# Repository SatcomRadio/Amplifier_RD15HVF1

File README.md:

# RD15HVF1 Amplifier for 280-320 mhz

This repo consists of a board that uses the RD15HVF1 amplifier at satcom frequency range (280-320Mhz).  

#### Please make sure to visit the [satcom radio website](https://satcomradio.github.io/) for more information

------

## Important notes:

- Do not put more than 6W of input RF power. The max power output of this PA is around 20W. Check the datasheet.
- You will need a tx/rx swith if you want to recieve when using this amplifier and also a lowpass filter to avoid it's harmonics!
- The recomended vias voltage is 2.7v. **Before soldering the amplifier adjust the potentiometer!**

- There are **a lot** of fake RD15HVF1 chips on aliexpress!  
- It's better to buy a used RD15HVF1 with the legs cut (as in [here](https://aliexpress.com/item/1005008441262750.html) than take the risk of buying a "new" one that is fake.

## Features:

- With 4W at 300mhz it gives an output of around 23W at 13.8v
- The input SWR is well tunned

## Aditional information:

- Be sure to use a proper heatsink. Ideally it should be 100x50mm. [This](https://aliexpress.com/item/1005004879389236.html) is the one I've got

- Apply thermal paste between the `RD15HVF1` amplifier and the heatsink
- The wound coils act as RF chokes. They should have between 150-300nH so wound a 0.7mm enameled wire around a 5mm drill bit for 6 turns
- The zener diode acts as a voltage limiter. Buy one with a breakdown voltage of around 4v so even if the potentiometer is open it will not push to the bias the 9v of the voltage regulator
- If the amplifier is not properly bolted to the heatsink or the coils are not correct, the output power will oscilate.
- If you buy one of those cheap black amplifiers of 4W for HF,VHF on aliexpress and connect a hackrf to it before connecting it to this amplifier, you'll get an output power of around 16W.
------

## Ordering the PCB:

Download the [GERBER-Amplifier](./GERBER-Amplifier.zip) file from this repo and order it a jlcpcb with the default options.  
The only option I've changed is to remove the manufacture code mark

------

## Prototype image:

------

## Output power:

### 2W input

| Freq in Mhz | Output power (W) |
|-------------|------------------|
| 270 | 14.3 |
| 280 | 16.5 |
| 290 | 15.5 |
| 300 | 14.5 |
| 310 | 14.1 |
| 320 | 13.3 |

At 4W input power the output is >20W

------

## BOM:

```
- PCB that you can order ar jlcpcb or somewhere else.
- RD15HVF1 (https://aliexpress.com/item/1005008441262750.html)
- 0805 560p Capacitor
- 0805 27p Capacitor
- 0805 62p Capacitor
- 0805 36p Capacitor
- 0805 8p Capacitor
- 0805 100p Capacitor
- 2x 1812 100n Capacitor
- 2x 1812 1u Capacitor
- 0805 10 ohm resistor
- 0805 1k ohm resistor
- L7809  9v voltage regulator
- 33uF SMD electrolitic cap 25v 5X5.4mm (https://aliexpress.com/item/1005005427427871.html)
- 3314G 10k potentiometer (https://aliexpress.com/item/1005003118598266.html)
- 100x50x50mm heatsink (https://aliexpress.com/item/1005004879389236.html)
- 0.7mm enameled wire for making air wound coils
- 2x SMA connectors
- (Optional) LL41 SMD 3v9 or 4v7 Zener Diode (Voltage limiter)
```

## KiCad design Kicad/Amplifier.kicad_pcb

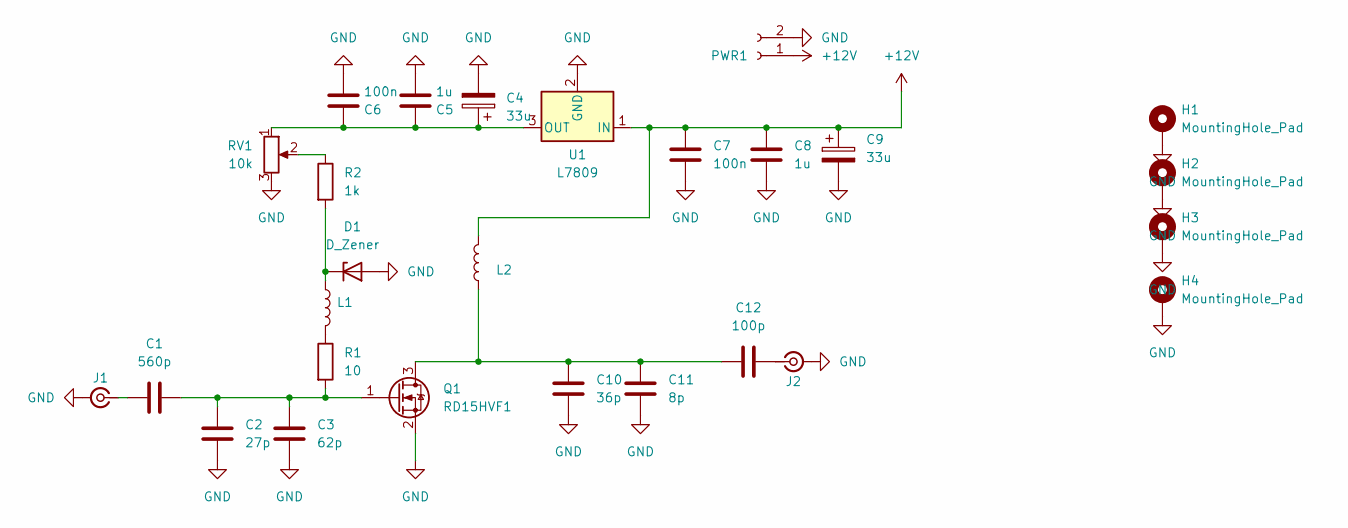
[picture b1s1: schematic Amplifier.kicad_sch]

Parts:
C1: 560p; C_0805_2012Metric_Pad1.18x1.45mm_HandSolder
C2: 27p; C_0805_2012Metric_Pad1.18x1.45mm_HandSolder
C3: 62p; C_0805_2012Metric_Pad1.18x1.45mm_HandSolder
C4, C9: 33u; CP_Elec_5x5.4
C5, C8: 1u; C_1812_4532Metric_Pad1.57x3.40mm_HandSolder
C6, C7: 100n; C_1812_4532Metric_Pad1.57x3.40mm_HandSolder
C10: 36p; C_0805_2012Metric_Pad1.18x1.45mm_HandSolder
C11: 8p; C_0805_2012Metric_Pad1.18x1.45mm_HandSolder
C12: 100p; C_0805_2012Metric_Pad1.18x1.45mm_HandSolder
D1: D_Zener; D_MiniMELF_Handsoldering
H1, H2, H3, H4: MountingHole_Pad; MountingHole_3.2mm_M3_DIN965_Pad
J1, J2: SMA_Samtec_SMA-J-P-X-ST-EM1_EdgeMount
L1, L2: 300n; Wound_Inductor_L
PWR1: Conn_01x02_Socket; Power_Conn
Q1: RD15HVF1; TO-220 SMD
R1: 10; R_0805_2012Metric_Pad1.20x1.40mm_HandSolder
R2: 1k; R_0805_2012Metric_Pad1.20x1.40mm_HandSolder
RV1: 10k; Potentiometer_Bourns_3314G_Vertical
U1: L7809; TO-220 SMD

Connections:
+12V: C7.2, C8.2, C9.1, L2.2, PWR1.1, U1.1 (IN)
GND: C2.1, C3.1, C4.2, C5.1, C6.1, C7.1, C8.1, C9.2, C10.1, C11.1, D1.2 (A), H1.1, H2.1, H3.1, H4.1, J1.2 (Ext), J2.2 (Ext), PWR1.2, Q1.2 (S), RV1.3, U1.2 (GND)
unnamed: D1.1 (K), L1.1, R2.2
unnamed: C1.1, J1.1 (In)
unnamed: C12.2, J2.1 (In)
unnamed: L1.2, R1.1
unnamed: C10.2, C11.2, C12.1, L2.1, Q1.3 (D)
unnamed: C1.2, C2.2, C3.2, Q1.1 (G), R1.2
unnamed: R2.1, RV1.2
unnamed: C4.1, C5.2, C6.2, RV1.1, U1.3 (OUT)

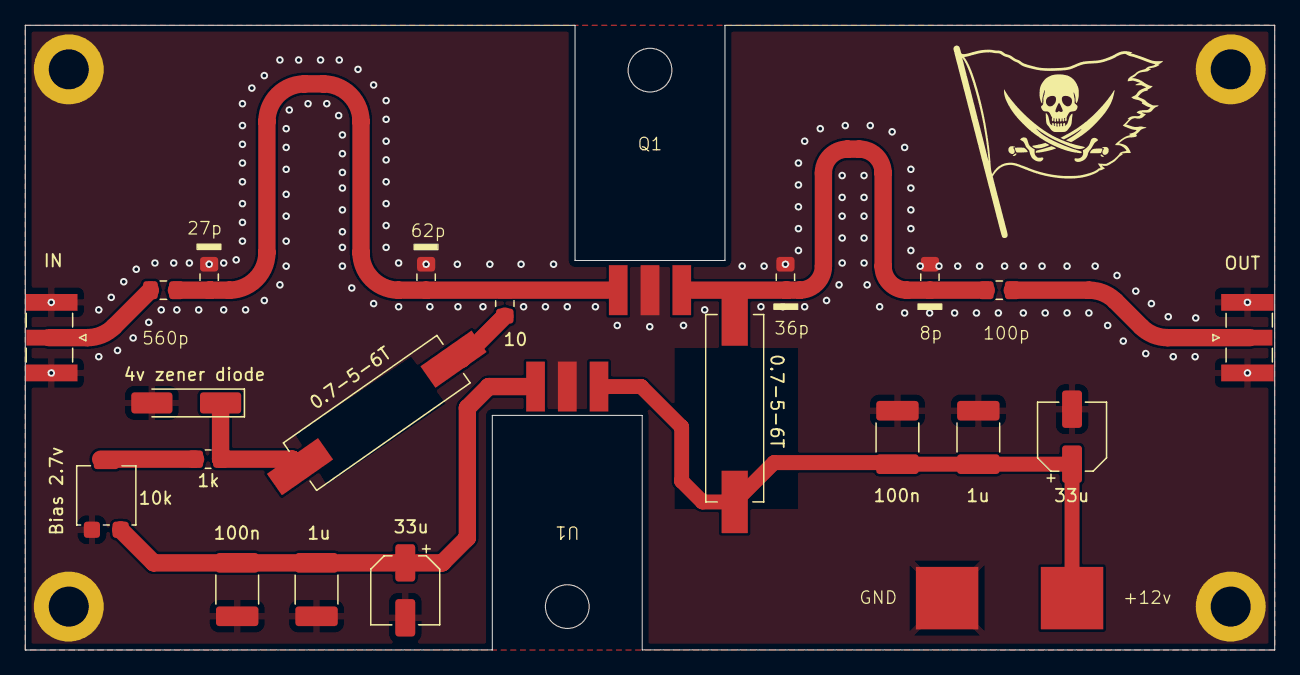
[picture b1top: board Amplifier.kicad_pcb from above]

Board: 2 copper layers, 100.0 x 50.0 mm, 27 parts (0 on the bottom side), 10 nets.

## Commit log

2025-05-10 Fix BOM
2025-05-10 Add gitignore
2025-05-10 Update links
2025-05-10 Added info
2025-05-10 Fix typos
2025-05-10 Fix capacitor, added more info
